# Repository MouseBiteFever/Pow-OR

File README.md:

Pow-OR
======

Power multiplexer

This will be a repository for the Eagle CAD design files of the Pow-OR power multiplexer board.
<br>To follow development of the board please go to http://MouseBiteFever.tumblr.com
<br><br>
A few video demonstrations of the Pow-OR board on can be foud on youtube at http://www.youtube.com/channel/UCmLNvzKj7SQ2D3ENkpwOFEA
<br><br>
I have put a small number of these up for sale on Tindie, and I just added 10 more as of 7/28/14. I'll be updating the stock as I get chips in and assemble boards.<br>
https://www.tindie.com/products/MouseBiteFever/pow-or-v131/
<br><br>

<br />This work is licensed under a <a rel="license" href="http://creativecommons.org/licenses/by-sa/4.0/">Creative Commons Attribution-ShareAlike 4.0 International License</a>.

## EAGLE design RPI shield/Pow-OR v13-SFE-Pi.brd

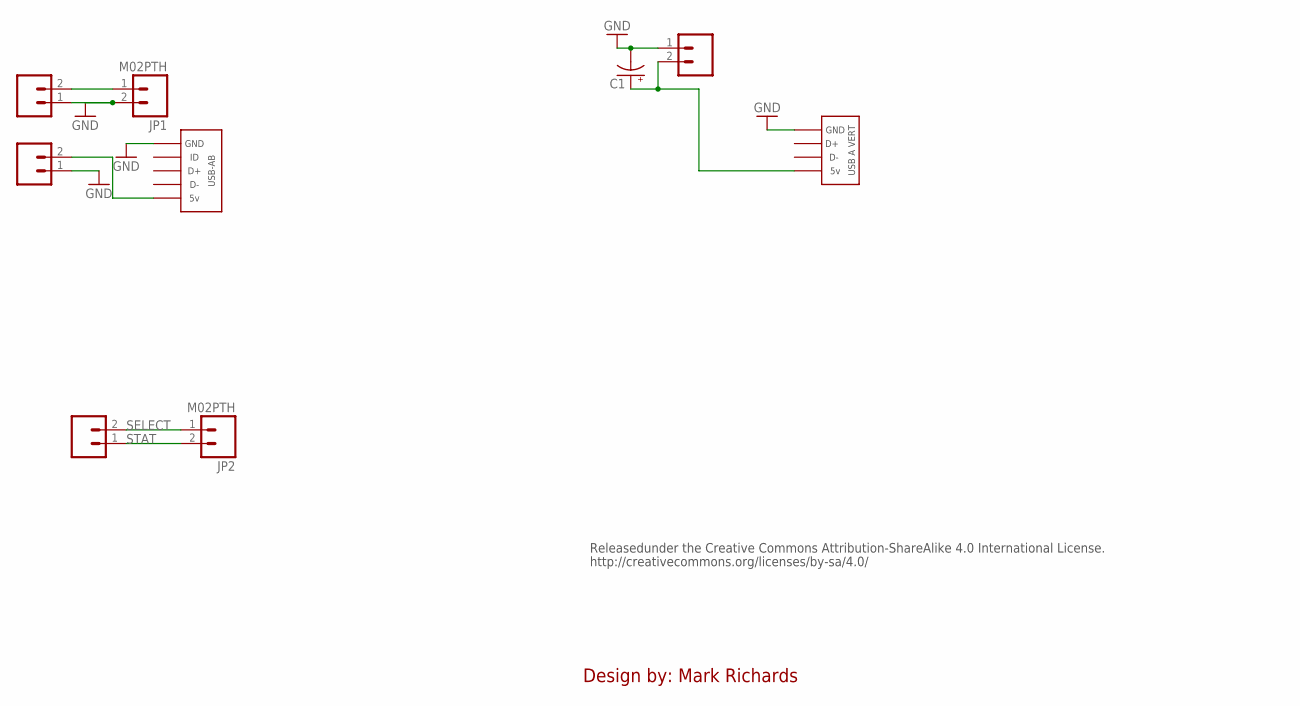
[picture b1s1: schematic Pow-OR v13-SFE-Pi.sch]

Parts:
C1: CAP_POLPTH1; CPOL-RADIAL-100UF-25V
JP1, JP2: M02PTH; 1X02
JP3, JP4, JP5, JP6: M021X02_NO_SILK; 1X02_NO_SILK
U$1: USB-AB
U$2: USBA-VERT

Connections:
GND: C1.2 (-), JP1.2, JP3.1, JP4.1, JP6.1, U$1.G, U$2.NEG (GND)
IN1: JP1.1, JP3.2
unnamed: JP4.2, U$1.V
OUT: C1.1 (+), JP6.2, U$2.VCC
SELECT: JP2.1, JP5.2
STAT: JP2.2, JP5.1

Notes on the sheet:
Releasedunder the Creative Commons Attribution-ShareAlike 4.0 International License.
http://creativecommons.org/licenses/by-sa/4.0/
Design by: Mark Richards

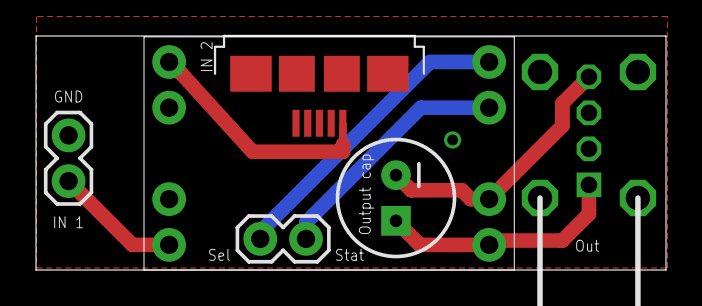
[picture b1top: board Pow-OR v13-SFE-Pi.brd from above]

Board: 2 copper layers, 35.0 x 13.0 mm, 9 parts (0 on the bottom side), 6 nets.

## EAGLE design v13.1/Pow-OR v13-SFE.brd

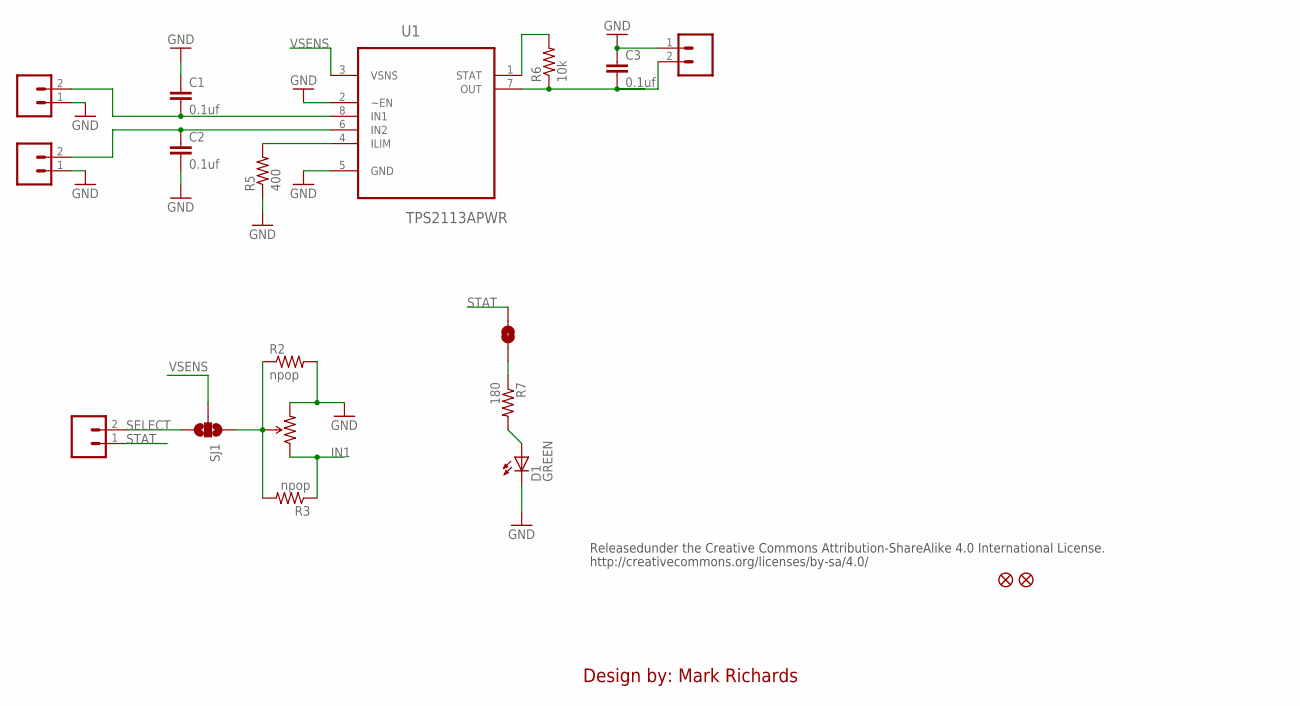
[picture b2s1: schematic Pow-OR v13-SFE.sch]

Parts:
C1, C2, C3: 0.1uf; 0603-CAP
D1: GREEN; LED-0603
FID1, FID2: FIDUCIAL1X2; FIDUCIAL-1X2
JP3, JP4, JP5, JP6: M021X02_NO_SILK; 1X02_NO_SILK
R1: TRIMPOT-PTH-KNOB; 3386U
R2, R3: npop; 0603-RES
R5: 400; 0603-RES
R6: 10k; 0603-RES
R7: 180; 0603-RES
SJ1: SOLDERJUMPER_2WAYPASTE1&2; SJ_3_PASTE1&2
SJ2: SOLDERJUMPERNC2; SJ_2S-NOTRACE
U1: TPS2113APWR; SOP65P640X120-8N

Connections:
GND: C1.1, C2.2, C3.1, D1.C, JP3.1, JP4.1, JP6.1, R1.3 (CW), R2.2, R5.1, U1.2 (~EN), U1.5 (GND)
ILIM: R5.2, U1.4 (ILIM)
IN1: C1.2, JP3.2, R1.1 (CCW), R3.1, U1.8 (IN1)
IN2: C2.1, JP4.2, U1.6 (IN2)
unnamed: D1.A, R7.2
unnamed: R1.2 (WIPER), R2.1, R3.2, SJ1.1
unnamed: R7.1, SJ2.1
OUT: C3.2, JP6.2, R6.1, U1.7 (OUT)
SELECT: JP5.2, SJ1.3
STAT: JP5.1, R6.2, SJ2.2, U1.1 (STAT)
VSENS: SJ1.2, U1.3 (VSNS)

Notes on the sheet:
Releasedunder the Creative Commons Attribution-ShareAlike 4.0 International License.
http://creativecommons.org/licenses/by-sa/4.0/
Design by: Mark Richards

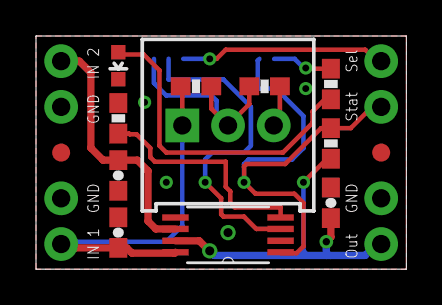
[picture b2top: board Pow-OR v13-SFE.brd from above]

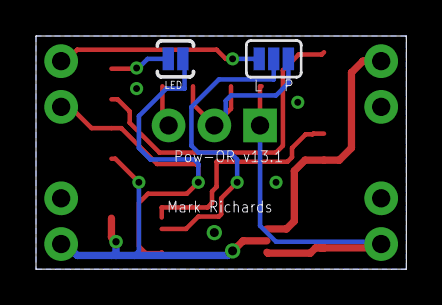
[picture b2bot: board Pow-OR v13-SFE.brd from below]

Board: 2 copper layers, 20.6 x 13.0 mm, 19 parts (2 on the bottom side), 11 nets.

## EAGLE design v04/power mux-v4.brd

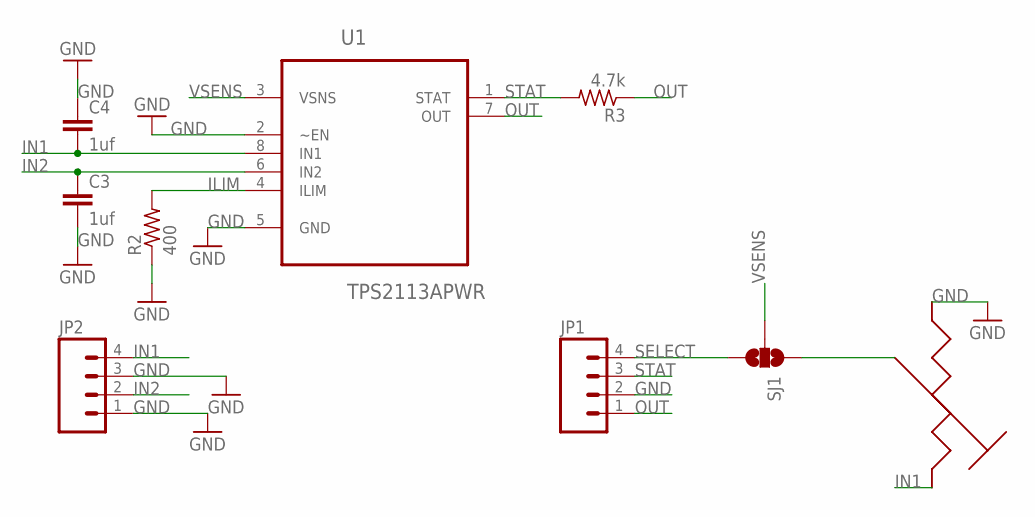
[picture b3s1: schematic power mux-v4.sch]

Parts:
C3, C4: 1uf; 0402-CAP
JP1, JP2: M04PTH; 1X04
R2: 400; R0402
R3: 4.7k; R0402
SJ1: SOLDERJUMPER_2WAYPASTE1&2; SJ_3_PASTE1&2
U1: TPS2113APWR; SOP65P640X120-8N
U$2: TRIMPOT-10K

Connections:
GND: C3.2, C4.1, JP1.2, JP2.1, JP2.3, R2.1, U1.2 (~EN), U1.5 (GND), U$2.1 (IN)
ILIM: R2.2, U1.4 (ILIM)
IN1: C4.2, JP2.4, U1.8 (IN1), U$2.2 (OUT)
IN2: C3.1, JP2.2, U1.6 (IN2)
unnamed: SJ1.1, U$2.3 (W)
OUT: JP1.1, R3.1, U1.7 (OUT)
SELECT: JP1.4, SJ1.3
STAT: JP1.3, R3.2, U1.1 (STAT)
VSENS: SJ1.2, U1.3 (VSNS)

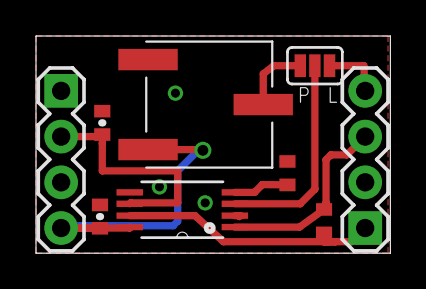
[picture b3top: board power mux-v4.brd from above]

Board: 2 copper layers, 19.7 x 12.1 mm, 9 parts (0 on the bottom side), 9 nets.

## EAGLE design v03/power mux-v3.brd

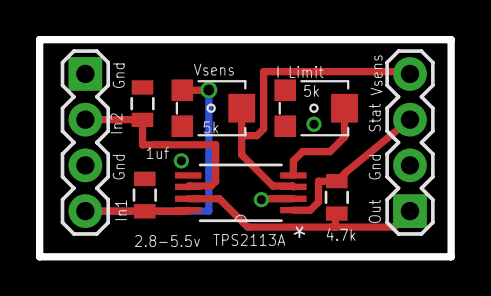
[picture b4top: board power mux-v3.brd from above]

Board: 2 copper layers, 22.9 x 12.1 mm, 8 parts (0 on the bottom side), 7 nets.

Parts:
C1, C2: 0805
JP1, JP2: 1X04
R1: 4.7k; 0805
U1: TPS2113APWR; SOP65P640X120-8N
U$1, U$2: TC33X-2

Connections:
GND: C1.2, C2.2, JP1.2, JP2.1, JP2.3, U1.2, U1.5, U$1.O1, U$2.O1
ILIM: U1.4, U$2.V
IN1: C1.1, JP2.4, U1.8, U$1.I1
IN2: C2.1, JP2.2, U1.6
OUT: JP1.1, R1.2, U1.7
STAT: JP1.3, R1.1, U1.1
VSENS: JP1.4, U1.3, U$1.V

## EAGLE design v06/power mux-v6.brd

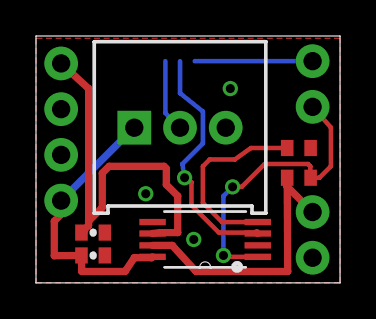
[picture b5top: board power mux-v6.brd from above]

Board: 2 copper layers, 16.9 x 13.7 mm, 11 parts (1 on the bottom side), 9 nets.

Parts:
C3, C4: 1uf; 0402-CAP
JP3, JP4, JP5, JP6: M021X02_NO_SILK; 1X02_NO_SILK
R1: TRIMPOT-PTH-KNOB; 3386U
R2: 400; R0402
R3: 4.7k; R0402
SJ1: SJ_3_PASTE1&2
U1: TPS2113APWR; SOP65P640X120-8N

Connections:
GND: C3.2, C4.1, JP3.1, JP4.1, JP6.1, R1.3, R2.1, U1.2, U1.5
ILIM: R2.2, U1.4
IN1: C4.2, JP3.2, R1.1, U1.8
IN2: C3.1, JP4.2, U1.6
unnamed: R1.2, SJ1.1
OUT: JP6.2, R3.1, U1.7
SELECT: JP5.2, SJ1.3
STAT: JP5.1, R3.2, U1.1
VSENS: SJ1.2, U1.3

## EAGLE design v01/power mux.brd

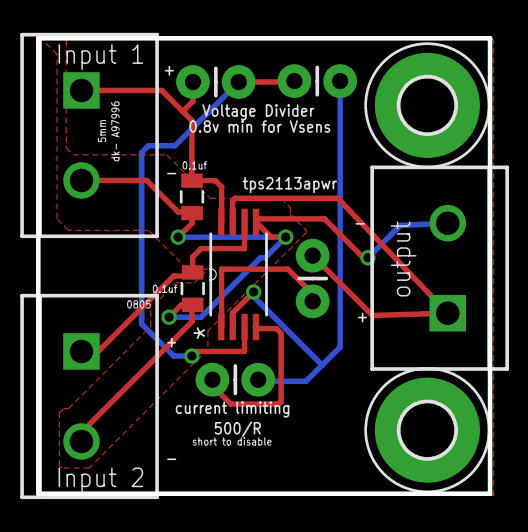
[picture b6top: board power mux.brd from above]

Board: 2 copper layers, 25.1 x 25.3 mm, 12 parts (0 on the bottom side), 8 nets.

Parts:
C1, C2: 0805
H1, H2: MOUNT-PAD-ROUND3.0; 3,0-PAD
JP1, JP2, JP4: M025MM; SCREWTERMINAL-5MM-2
R1, R2, R3, R4: AXIAL-0.1
U1: TPS2113APWR; SOP65P640X120-8N

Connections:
GND: C1.2, C2.2, JP1.2, JP2.2, JP4.2, U1.5
GND6: R2.P$1, R3.P$1, U1.2
ILIM: R3.P$2, U1.4
IN1+: C1.1, JP2.1, R1.P$2, U1.8
IN2+: C2.1, JP4.1, U1.6
unnamed: R4.P$2, U1.1
OUT: JP1.1, R4.P$1, U1.7
VSENS: R1.P$1, R2.P$2, U1.3

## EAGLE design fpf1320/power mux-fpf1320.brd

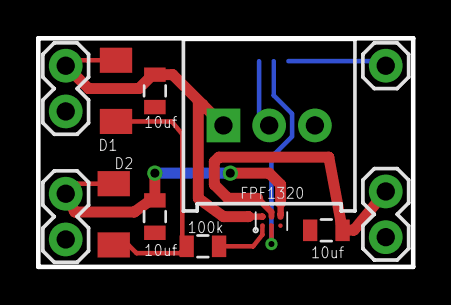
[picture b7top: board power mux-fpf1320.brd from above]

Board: 2 copper layers, 20.8 x 12.7 mm, 13 parts (1 on the bottom side), 9 nets.

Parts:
C1, C2, C3: 10uf; 0805
D1, D2: LL4148FSCT-ND; SOD80
JP1, JP2, JP3: M02PTH; 1X02
JP4: M01PTH; 1X01
R1: TRIMPOT-PTH-KNOB; 3386U
R2: 100k; 0805
SJ2: SJ_3_PASTE1&2
U$3: FPF1320; 6-UFBGA

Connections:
GND: C1.2, C2.2, C3.2, JP1.1, JP2.1, JP3.1, R1.3, U$3.GND
unnamed: D1.1, D2.1, R2.1
unnamed: R2.2, U$3.EN
unnamed: SJ2.2, U$3.SEL
SEL: R1.2, SJ2.3
SELJ: JP4.1, SJ2.1
VINA: C1.1, D1.2, JP1.2, R1.1, U$3.VINA
VINB: C2.1, D2.2, JP2.2, U$3.VINB
VOUT: C3.1, JP3.2, U$3.VOUT

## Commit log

2014-05-03 Eagle CAD design files
    All versions to date.
2014-05-03 Board Images
    Added images of all the boards.
2014-05-03 Reorganization
    Pulled all files out of the pow-or folder
2014-05-03 Folder Renaming
    constant naming scheme
2014-05-03 Added Documentation
    Simple hookup and usage guide.
2014-05-25 Minor changes
    cleaned up schematic, added fiducials, etc
2014-05-31 Updated Documentation
    added volt ranges, remade pdf
2014-07-17 Added Raspberry Pi Shield
    Added V1
2014-07-22 Schematics
    schematics for v13.1
2014-07-23 summary update
    added youtube page link for videos
2014-07-23 wording update
    wording update
2014-07-23 schematics
    duplicating the sch pdf in the v13.1 folder
2014-07-25 update readme
    add tindie link
2014-07-29 update readme
    updated stock on tindie

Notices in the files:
parts and their libraries:
SparkFun-Connectors: Licensing: CC v3.0 Share-Alike You are welcome to use this library for commercial purposes.
